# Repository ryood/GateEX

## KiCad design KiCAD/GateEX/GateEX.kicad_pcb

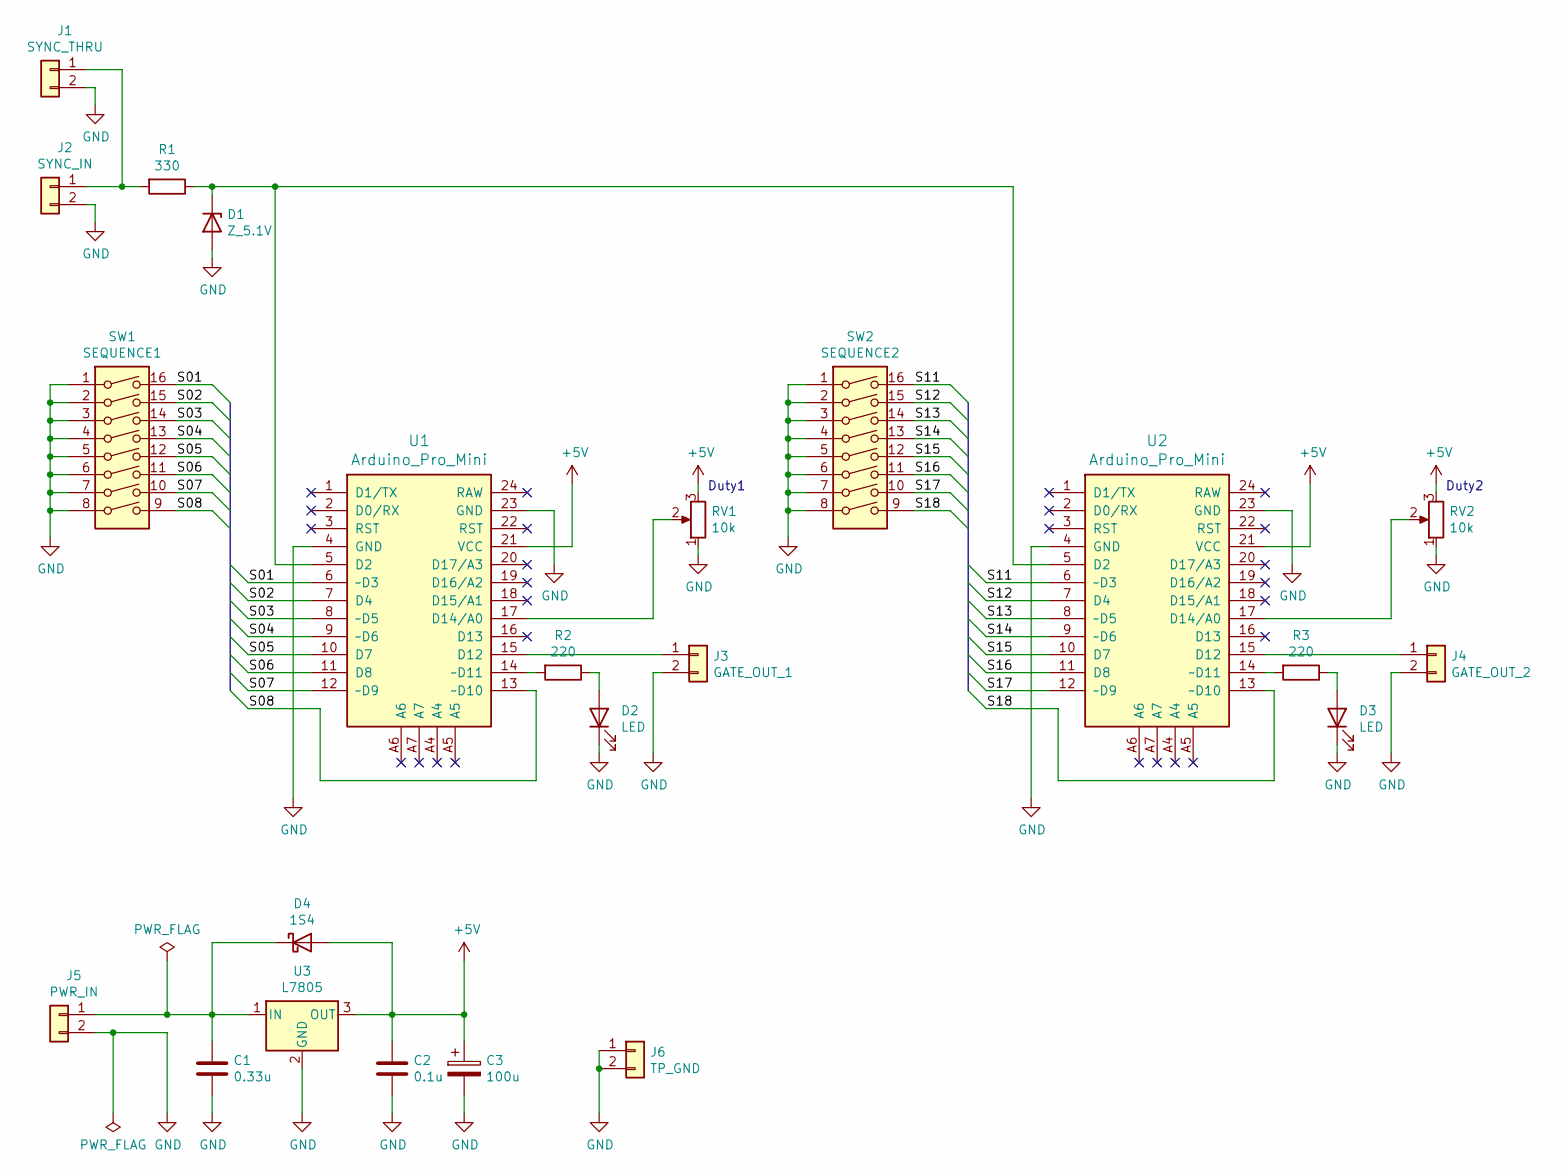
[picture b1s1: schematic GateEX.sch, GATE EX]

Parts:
C1: 0.33u; C_Disc_D3.0mm_W1.6mm_P2.50mm
C2: 0.1u; C_Disc_D3.0mm_W1.6mm_P2.50mm
C3: 100u; CP_Radial_D6.3mm_P2.50mm
D1: Z_5.1V; D_DO-35_SOD27_P7.62mm_Horizontal
D2, D3: LED; LED_D3.0mm
D4: 1S4; D_DO-35_SOD27_P7.62mm_Horizontal
J1: SYNC_THRU; JST_XH_B2B-XH-A_1x02_P2.50mm_Vertical
J2: SYNC_IN; JST_XH_B2B-XH-A_1x02_P2.50mm_Vertical
J3: GATE_OUT_1; JST_XH_B2B-XH-A_1x02_P2.50mm_Vertical
J4: GATE_OUT_2; JST_XH_B2B-XH-A_1x02_P2.50mm_Vertical
J5: PWR_IN; JST_XH_B2B-XH-A_1x02_P2.50mm_Vertical
J6: TP_GND; PinHeader_1x02_P2.54mm_Vertical
R1: 330; R_Axial_DIN0207_L6.3mm_D2.5mm_P7.62mm_Horizontal
R2, R3: 220; R_Axial_DIN0207_L6.3mm_D2.5mm_P2.54mm_Vertical
RV1, RV2: 10k; Potentiometer_Alps_RK097_Single_Horizontal
SW1: SEQUENCE1; SW_DIP_SPSTx08_Slide_9.78x22.5mm_W7.62mm_P2.54mm
SW2: SEQUENCE2; SW_DIP_SPSTx08_Slide_9.78x22.5mm_W7.62mm_P2.54mm
U1, U2: Arduino_Pro_Mini
U3: L7805; TO-220F-3_Vertical

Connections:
+5V: C2.1, C3.1, D4.2 (A), RV1.3, RV2.3, U1.21 (VCC), U2.21 (VCC), U3.3 (OUT)
/S01: SW1.16, U1.6 (~~D3)
/S02: SW1.15, U1.7 (D4)
/S03: SW1.14, U1.8 (~~D5)
/S04: SW1.13, U1.9 (~~D6)
/S05: SW1.12, U1.10 (D7)
/S06: SW1.11, U1.11 (D8)
/S07: SW1.10, U1.12 (~~D9)
/S08: SW1.9, U1.13 (~~D10)
/S11: SW2.16, U2.6 (~~D3)
/S12: SW2.15, U2.7 (D4)
/S13: SW2.14, U2.8 (~~D5)
/S14: SW2.13, U2.9 (~~D6)
/S15: SW2.12, U2.10 (D7)
/S16: SW2.11, U2.11 (D8)
/S17: SW2.10, U2.12 (~~D9)
/S18: SW2.9, U2.13 (~~D10)
GND: C1.2, C2.2, C3.2, D1.2 (A), D2.1 (K), D3.1 (K), J1.2, J2.2, J3.2, J4.2, J5.2, J6.1, J6.2, RV1.1, RV2.1, SW1.1, SW1.2, SW1.3, SW1.4, SW1.5, SW1.6, SW1.7, SW1.8, SW2.1, SW2.2, SW2.3, SW2.4, SW2.5, SW2.6, SW2.7, SW2.8, U1.4 (GND), U1.23 (GND), U2.4 (GND), U2.23 (GND), U3.2 (GND)
unnamed: C1.1, D4.1 (K), J5.1, U3.1 (IN)
unnamed: D1.1 (K), R1.1, U1.5 (D2), U2.5 (D2)
unnamed: D2.2 (A), R2.1
unnamed: D3.2 (A), R3.1
unnamed: J1.1, J2.1, R1.2
unnamed: J3.1, U1.15 (D12)
unnamed: J4.1, U2.15 (D12)
unnamed: R2.2, U1.14 (~~D11)
unnamed: R3.2, U2.14 (~~D11)
unnamed: RV1.2, U1.17 (D14/A0)
unnamed: RV2.2, U2.17 (D14/A0)

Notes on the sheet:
Duty2
Duty1

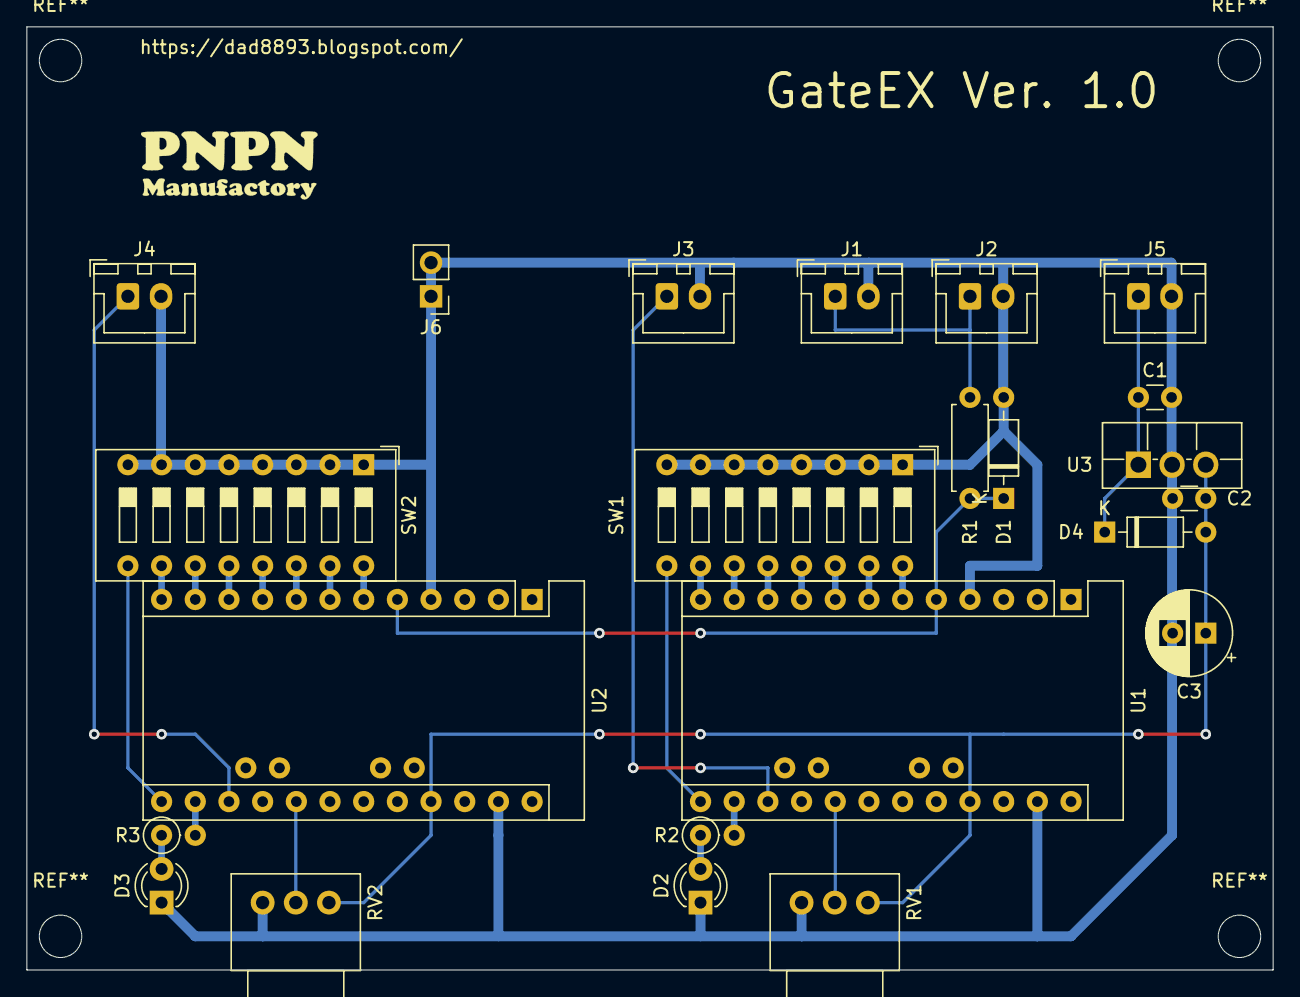
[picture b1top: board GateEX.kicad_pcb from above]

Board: 2 copper layers, 94.0 x 71.1 mm, 23 parts (0 on the bottom side), 29 nets.

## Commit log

2021-05-24 Comletion
2021-08-14 Sync Division
